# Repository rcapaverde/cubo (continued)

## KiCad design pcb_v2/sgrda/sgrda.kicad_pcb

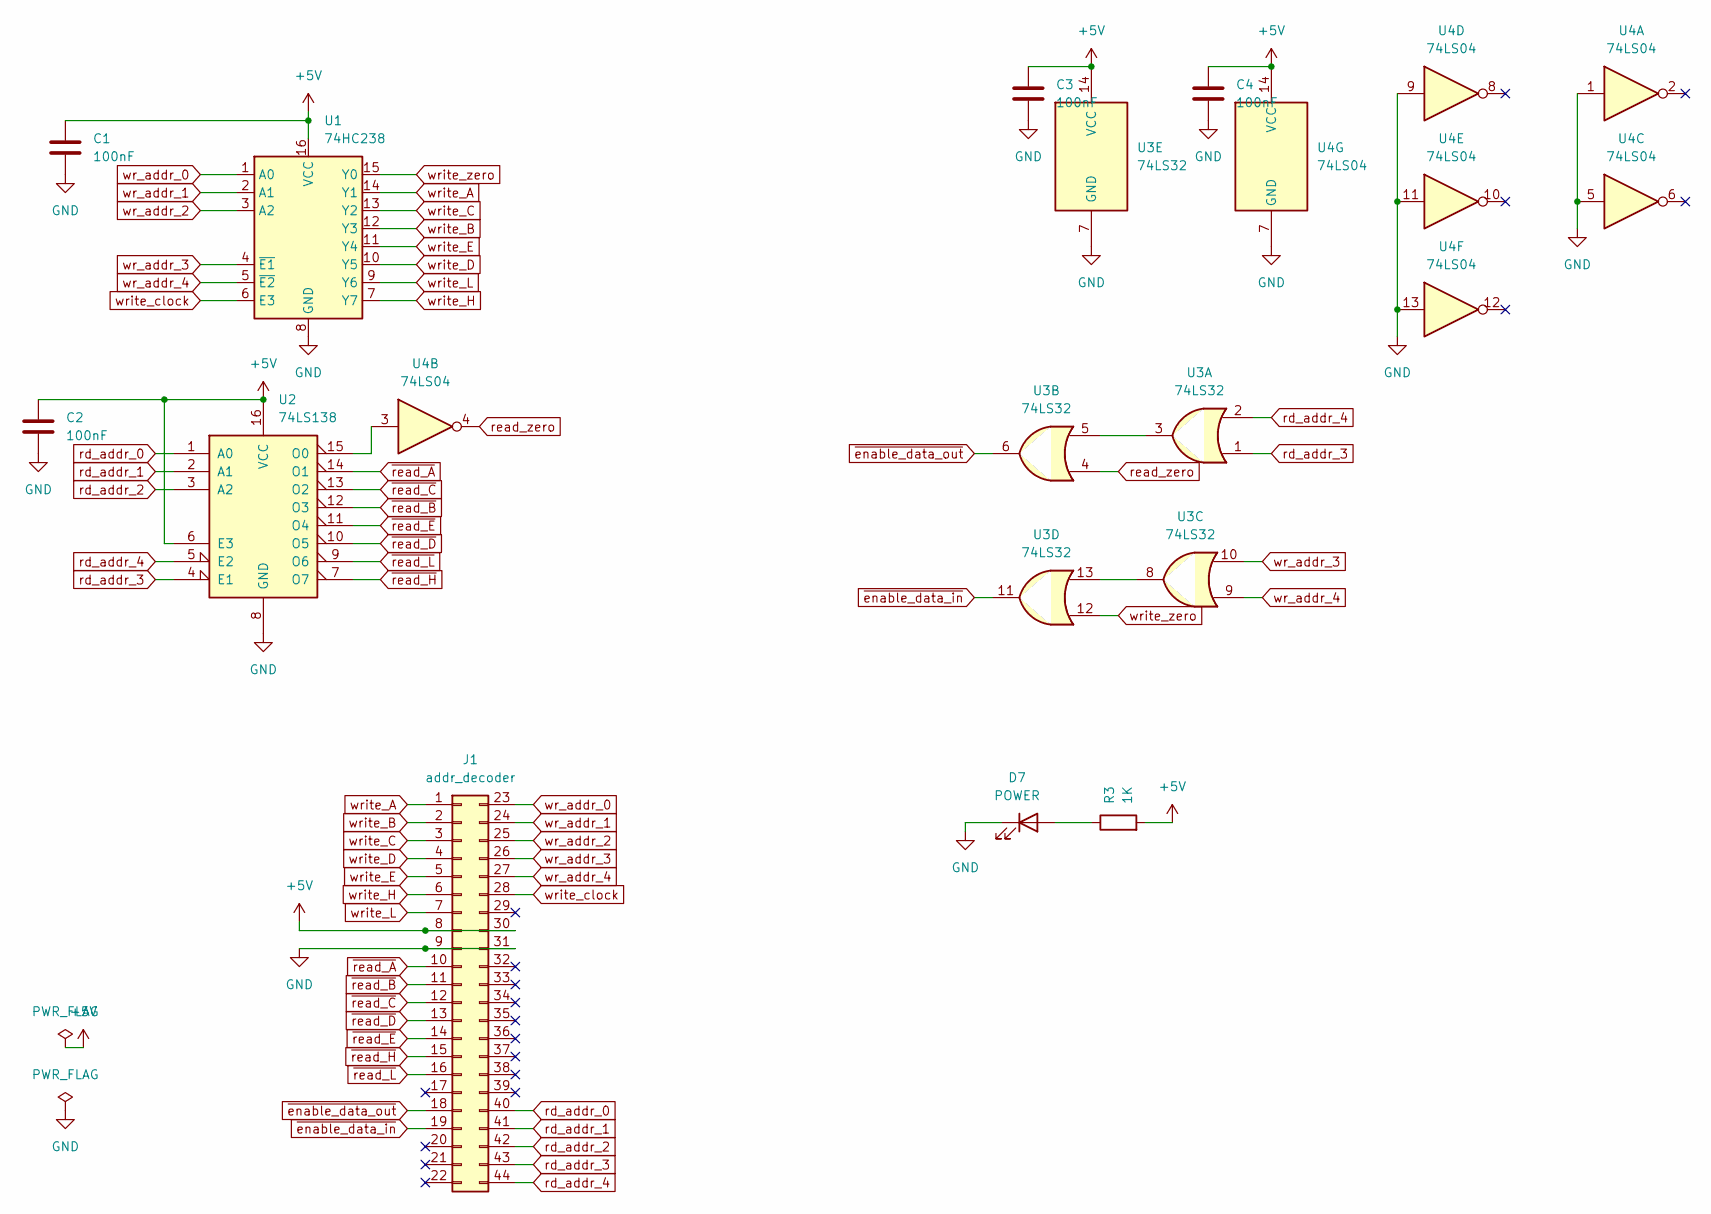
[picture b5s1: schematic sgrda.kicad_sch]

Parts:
C1, C2, C3, C4: 100nF; C_Disc_D4.7mm_W2.5mm_P5.00mm
D7: POWER; LED_D5.0mm
J1: addr_decoder; edge-connector-44
R3: 1K; R_Axial_DIN0207_L6.3mm_D2.5mm_P7.62mm_Horizontal
U1: 74HC238; DIP-16_W7.62mm
U2: 74LS138; DIP-16_W7.62mm
U3: 74LS32; DIP-14_W7.62mm
U4: 74LS04; DIP-14_W7.62mm

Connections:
+5V: C1.1, C2.1, C3.1, C4.1, J1.8, J1.30, R3.2, U1.16 (VCC), U2.6 (E3), U2.16 (VCC), U3.14 (VCC), U4.14 (VCC)
GND: C1.2, C2.2, C3.2, C4.2, D7.1 (K), J1.9, J1.31, U1.8 (GND), U2.8 (GND), U3.7 (GND), U4.1, U4.5, U4.7 (GND), U4.9, U4.11, U4.13
unnamed: D7.2 (A), R3.1
unnamed: U2.15 (O0), U4.3
unnamed: U3.3, U3.5
unnamed: U3.8, U3.13
rd_addr_0: J1.40, U2.1 (A0)
rd_addr_1: J1.41, U2.2 (A1)
rd_addr_2: J1.42, U2.3 (A2)
rd_addr_3: J1.43, U2.4 (E1), U3.1
rd_addr_4: J1.44, U2.5 (E2), U3.2
read_zero: U3.4, U4.4
wr_addr_0: J1.23, U1.1 (A0)
wr_addr_1: J1.24, U1.2 (A1)
wr_addr_2: J1.25, U1.3 (A2)
wr_addr_3: J1.26, U1.4 (~E1), U3.10
wr_addr_4: J1.27, U1.5 (~E2), U3.9
write_A: J1.1, U1.14 (Y1)
write_B: J1.2, U1.12 (Y3)
write_C: J1.3, U1.13 (Y2)
write_D: J1.4, U1.10 (Y5)
write_E: J1.5, U1.11 (Y4)
write_H: J1.6, U1.7 (Y7)
write_L: J1.7, U1.9 (Y6)
write_clock: J1.28, U1.6 (E3)
write_zero: U1.15 (Y0), U3.12
~enable_data_in: J1.19, U3.11
~enable_data_out: J1.18, U3.6
~read_A: J1.10, U2.14 (O1)
~read_B: J1.11, U2.12 (O3)
~read_C: J1.12, U2.13 (O2)
~read_D: J1.13, U2.10 (O5)
~read_E: J1.14, U2.11 (O4)
~read_H: J1.15, U2.7 (O7)
~read_L: J1.16, U2.9 (O6)

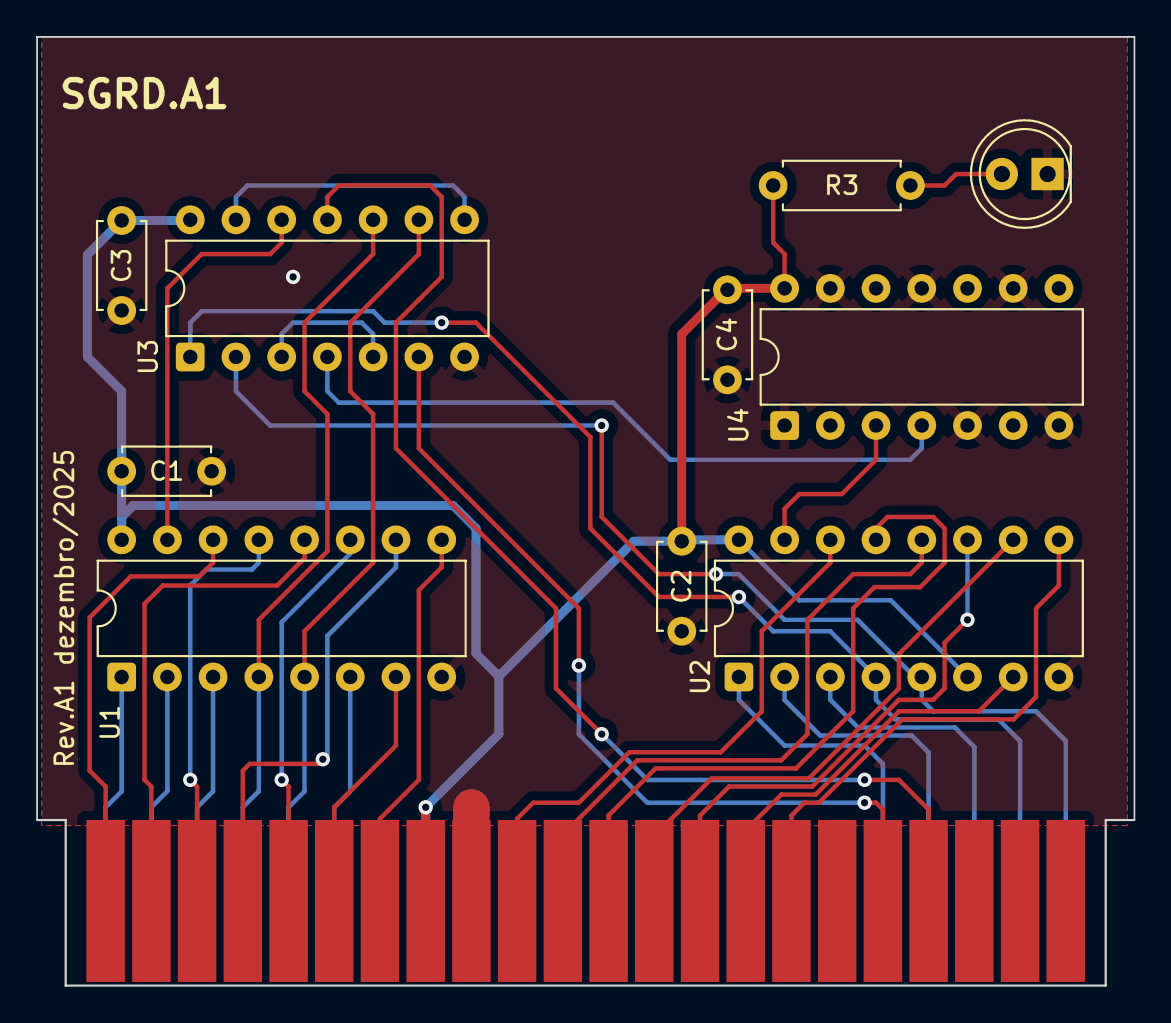
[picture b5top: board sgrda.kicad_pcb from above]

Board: 2 copper layers, 61.0 x 52.7 mm, 11 parts (0 on the bottom side), 35 nets.

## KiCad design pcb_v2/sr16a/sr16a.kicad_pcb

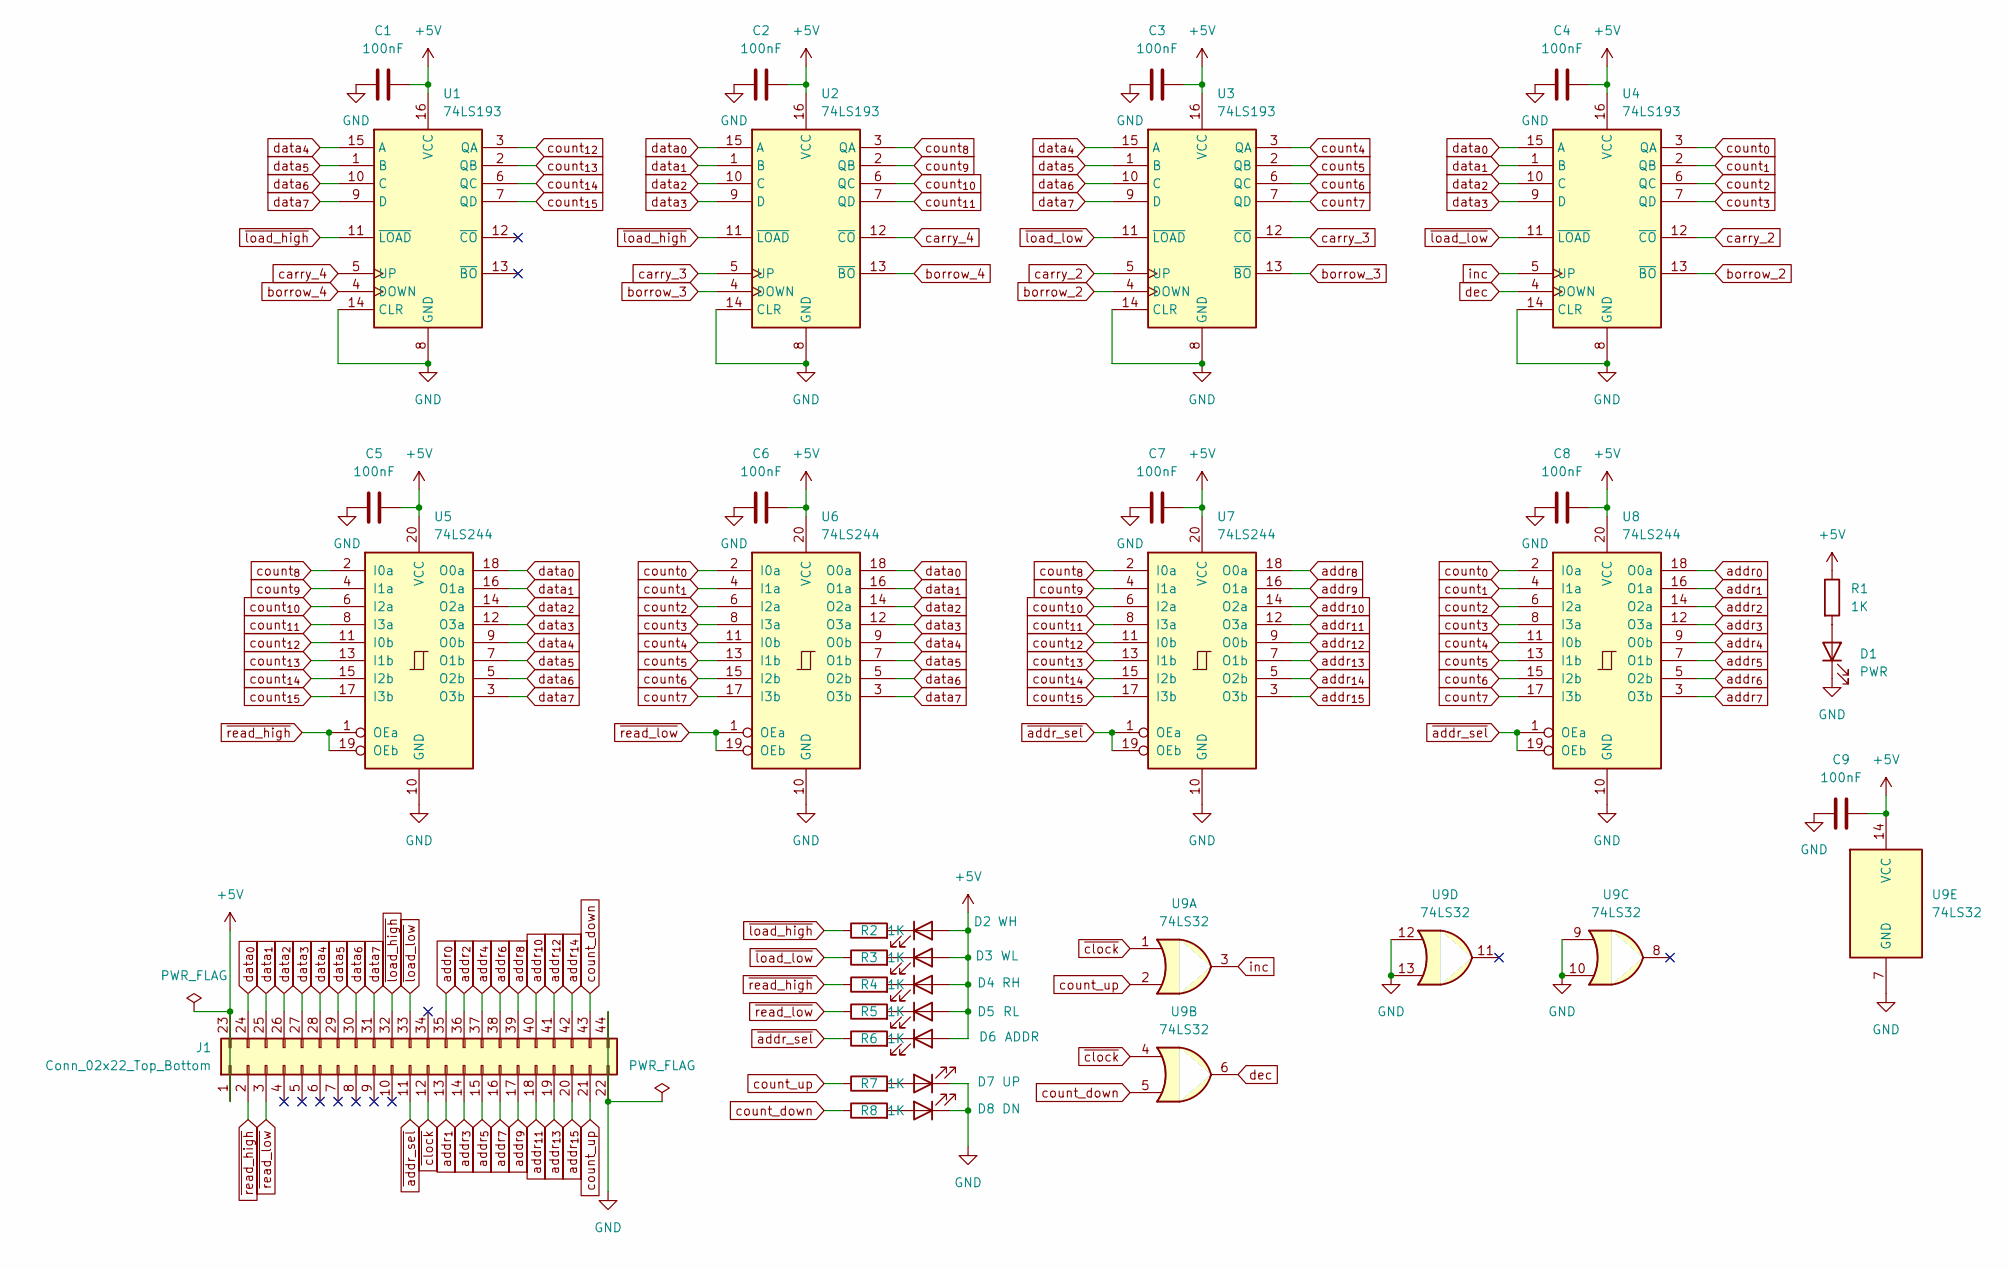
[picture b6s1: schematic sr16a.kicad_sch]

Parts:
C1, C2, C3, C4, C5, C6, C7, C8, C9: 100nF; C_Disc_D5.1mm_W3.2mm_P5.00mm
D1: PWR; LED_D5.0mm
D2: WH; LED_D5.0mm
D3: WL; LED_D5.0mm
D4: RH; LED_D5.0mm
D5: RL; LED_D5.0mm
D6: ADDR; LED_D5.0mm
D7: UP; LED_D5.0mm
D8: DN; LED_D5.0mm
J1: Conn_02x22_Top_Bottom; edge-connector-44
R1, R2, R3, R4, R5, R6, R7, R8: 1K; R_Axial_DIN0204_L3.6mm_D1.6mm_P7.62mm_Horizontal
U1, U2, U3, U4: 74LS193; DIP-16_W7.62mm
U5, U6, U7, U8: 74LS244; DIP-20_W7.62mm
U9: 74LS32; DIP-14_W7.62mm

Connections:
+5V: C1.2, C2.2, C3.2, C4.2, C5.2, C6.2, C7.2, C8.2, C9.2, D2.2 (A), D3.2 (A), D4.2 (A), D5.2 (A), D6.2 (A), J1.1, J1.23, R1.1, U1.16 (VCC), U2.16 (VCC), U3.16 (VCC), U4.16 (VCC), U5.20 (VCC), U6.20 (VCC), U7.20 (VCC), U8.20 (VCC), U9.14 (VCC)
GND: C1.1, C2.1, C3.1, C4.1, C5.1, C6.1, C7.1, C8.1, C9.1, D1.1 (K), D7.1 (K), D8.1 (K), J1.22, J1.44, U1.8 (GND), U1.14 (CLR), U2.8 (GND), U2.14 (CLR), U3.8 (GND), U3.14 (CLR), U4.8 (GND), U4.14 (CLR), U5.10 (GND), U6.10 (GND), U7.10 (GND), U8.10 (GND), U9.7 (GND), U9.9, U9.10, U9.12, U9.13
unnamed: D1.2 (A), R1.2
unnamed: D2.1 (K), R2.2
unnamed: D3.1 (K), R3.2
unnamed: D4.1 (K), R4.2
unnamed: D5.1 (K), R5.2
unnamed: D6.1 (K), R6.2
unnamed: D7.2 (A), R7.2
unnamed: D8.2 (A), R8.2
addr_{0}: J1.35, U8.18 (O0a)
addr_{1}: J1.13, U8.16 (O1a)
addr_{2}: J1.36, U8.14 (O2a)
addr_{3}: J1.14, U8.12 (O3a)
addr_{4}: J1.37, U8.9 (O0b)
addr_{5}: J1.15, U8.7 (O1b)
addr_{6}: J1.38, U8.5 (O2b)
addr_{7}: J1.16, U8.3 (O3b)
addr_{8}: J1.39, U7.18 (O0a)
addr_{9}: J1.17, U7.16 (O1a)
addr_{10}: J1.40, U7.14 (O2a)
addr_{11}: J1.18, U7.12 (O3a)
addr_{12}: J1.41, U7.9 (O0b)
addr_{13}: J1.19, U7.7 (O1b)
addr_{14}: J1.42, U7.5 (O2b)
addr_{15}: J1.20, U7.3 (O3b)
borrow_2: U3.4 (DOWN), U4.13 (~BO)
borrow_3: U2.4 (DOWN), U3.13 (~BO)
borrow_4: U1.4 (DOWN), U2.13 (~BO)
carry_2: U3.5 (UP), U4.12 (~CO)
carry_3: U2.5 (UP), U3.12 (~CO)
carry_4: U1.5 (UP), U2.12 (~CO)
count_down: J1.43, R8.1, U9.5
count_up: J1.21, R7.1, U9.2
count_{0}: U4.3 (QA), U6.2 (I0a), U8.2 (I0a)
count_{1}: U4.2 (QB), U6.4 (I1a), U8.4 (I1a)
count_{2}: U4.6 (QC), U6.6 (I2a), U8.6 (I2a)
count_{3}: U4.7 (QD), U6.8 (I3a), U8.8 (I3a)
count_{4}: U3.3 (QA), U6.11 (I0b), U8.11 (I0b)
count_{5}: U3.2 (QB), U6.13 (I1b), U8.13 (I1b)
count_{6}: U3.6 (QC), U6.15 (I2b), U8.15 (I2b)
count_{7}: U3.7 (QD), U6.17 (I3b), U8.17 (I3b)
count_{8}: U2.3 (QA), U5.2 (I0a), U7.2 (I0a)
count_{9}: U2.2 (QB), U5.4 (I1a), U7.4 (I1a)
count_{10}: U2.6 (QC), U5.6 (I2a), U7.6 (I2a)
count_{11}: U2.7 (QD), U5.8 (I3a), U7.8 (I3a)
count_{12}: U1.3 (QA), U5.11 (I0b), U7.11 (I0b)
count_{13}: U1.2 (QB), U5.13 (I1b), U7.13 (I1b)
count_{14}: U1.6 (QC), U5.15 (I2b), U7.15 (I2b)
count_{15}: U1.7 (QD), U5.17 (I3b), U7.17 (I3b)
data_{0}: J1.24, U2.15 (A), U4.15 (A), U5.18 (O0a), U6.18 (O0a)
data_{1}: J1.25, U2.1 (B), U4.1 (B), U5.16 (O1a), U6.16 (O1a)
data_{2}: J1.26, U2.10 (C), U4.10 (C), U5.14 (O2a), U6.14 (O2a)
data_{3}: J1.27, U2.9 (D), U4.9 (D), U5.12 (O3a), U6.12 (O3a)
data_{4}: J1.28, U1.15 (A), U3.15 (A), U5.9 (O0b), U6.9 (O0b)
data_{5}: J1.29, U1.1 (B), U3.1 (B), U5.7 (O1b), U6.7 (O1b)
data_{6}: J1.30, U1.10 (C), U3.10 (C), U5.5 (O2b), U6.5 (O2b)
data_{7}: J1.31, U1.9 (D), U3.9 (D), U5.3 (O3b), U6.3 (O3b)
dec: U4.4 (DOWN), U9.6
inc: U4.5 (UP), U9.3
~addr_sel: J1.11, R6.1, U7.1 (OEa), U7.19 (OEb), U8.1 (OEa), U8.19 (OEb)
~clock: J1.12, U9.1, U9.4
~load_high: J1.32, R2.1, U1.11 (~LOAD), U2.11 (~LOAD)
~load_low: J1.33, R3.1, U3.11 (~LOAD), U4.11 (~LOAD)
~read_high: J1.2, R4.1, U5.1 (OEa), U5.19 (OEb)
~read_low: J1.3, R5.1, U6.1 (OEa), U6.19 (OEb)

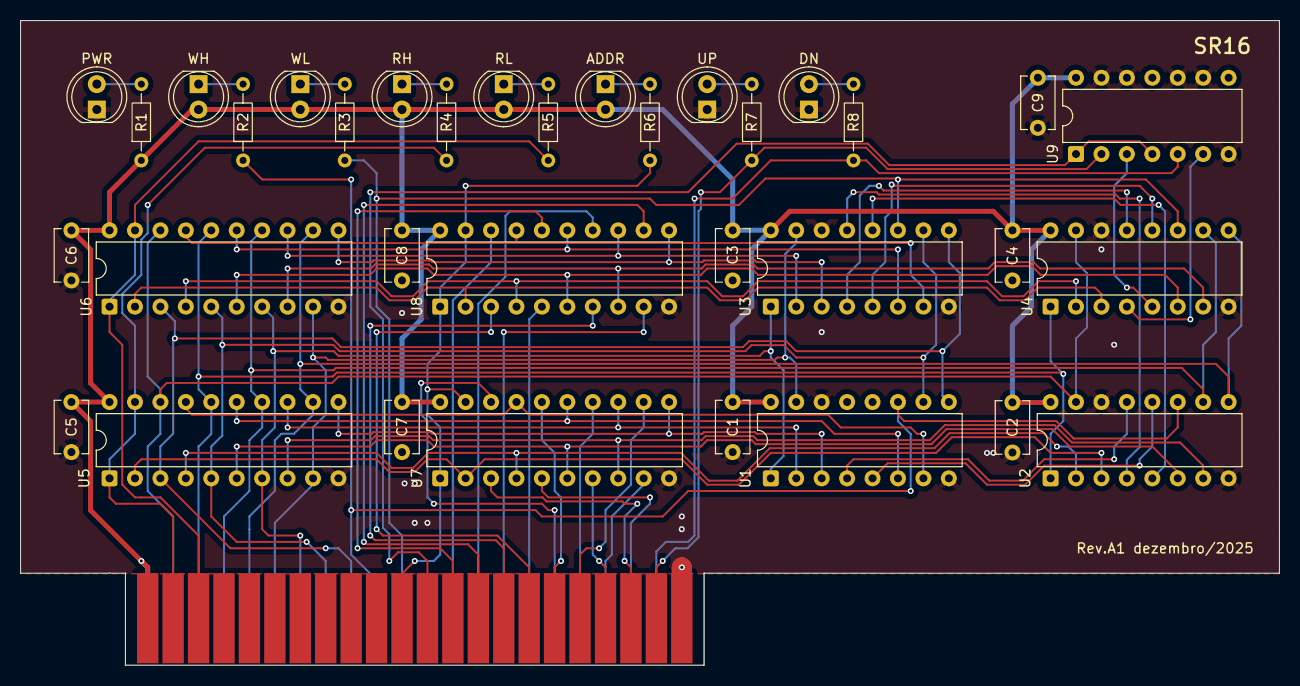
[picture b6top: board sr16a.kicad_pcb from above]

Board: 2 copper layers, 125.7 x 64.4 mm, 35 parts (0 on the bottom side), 66 nets.

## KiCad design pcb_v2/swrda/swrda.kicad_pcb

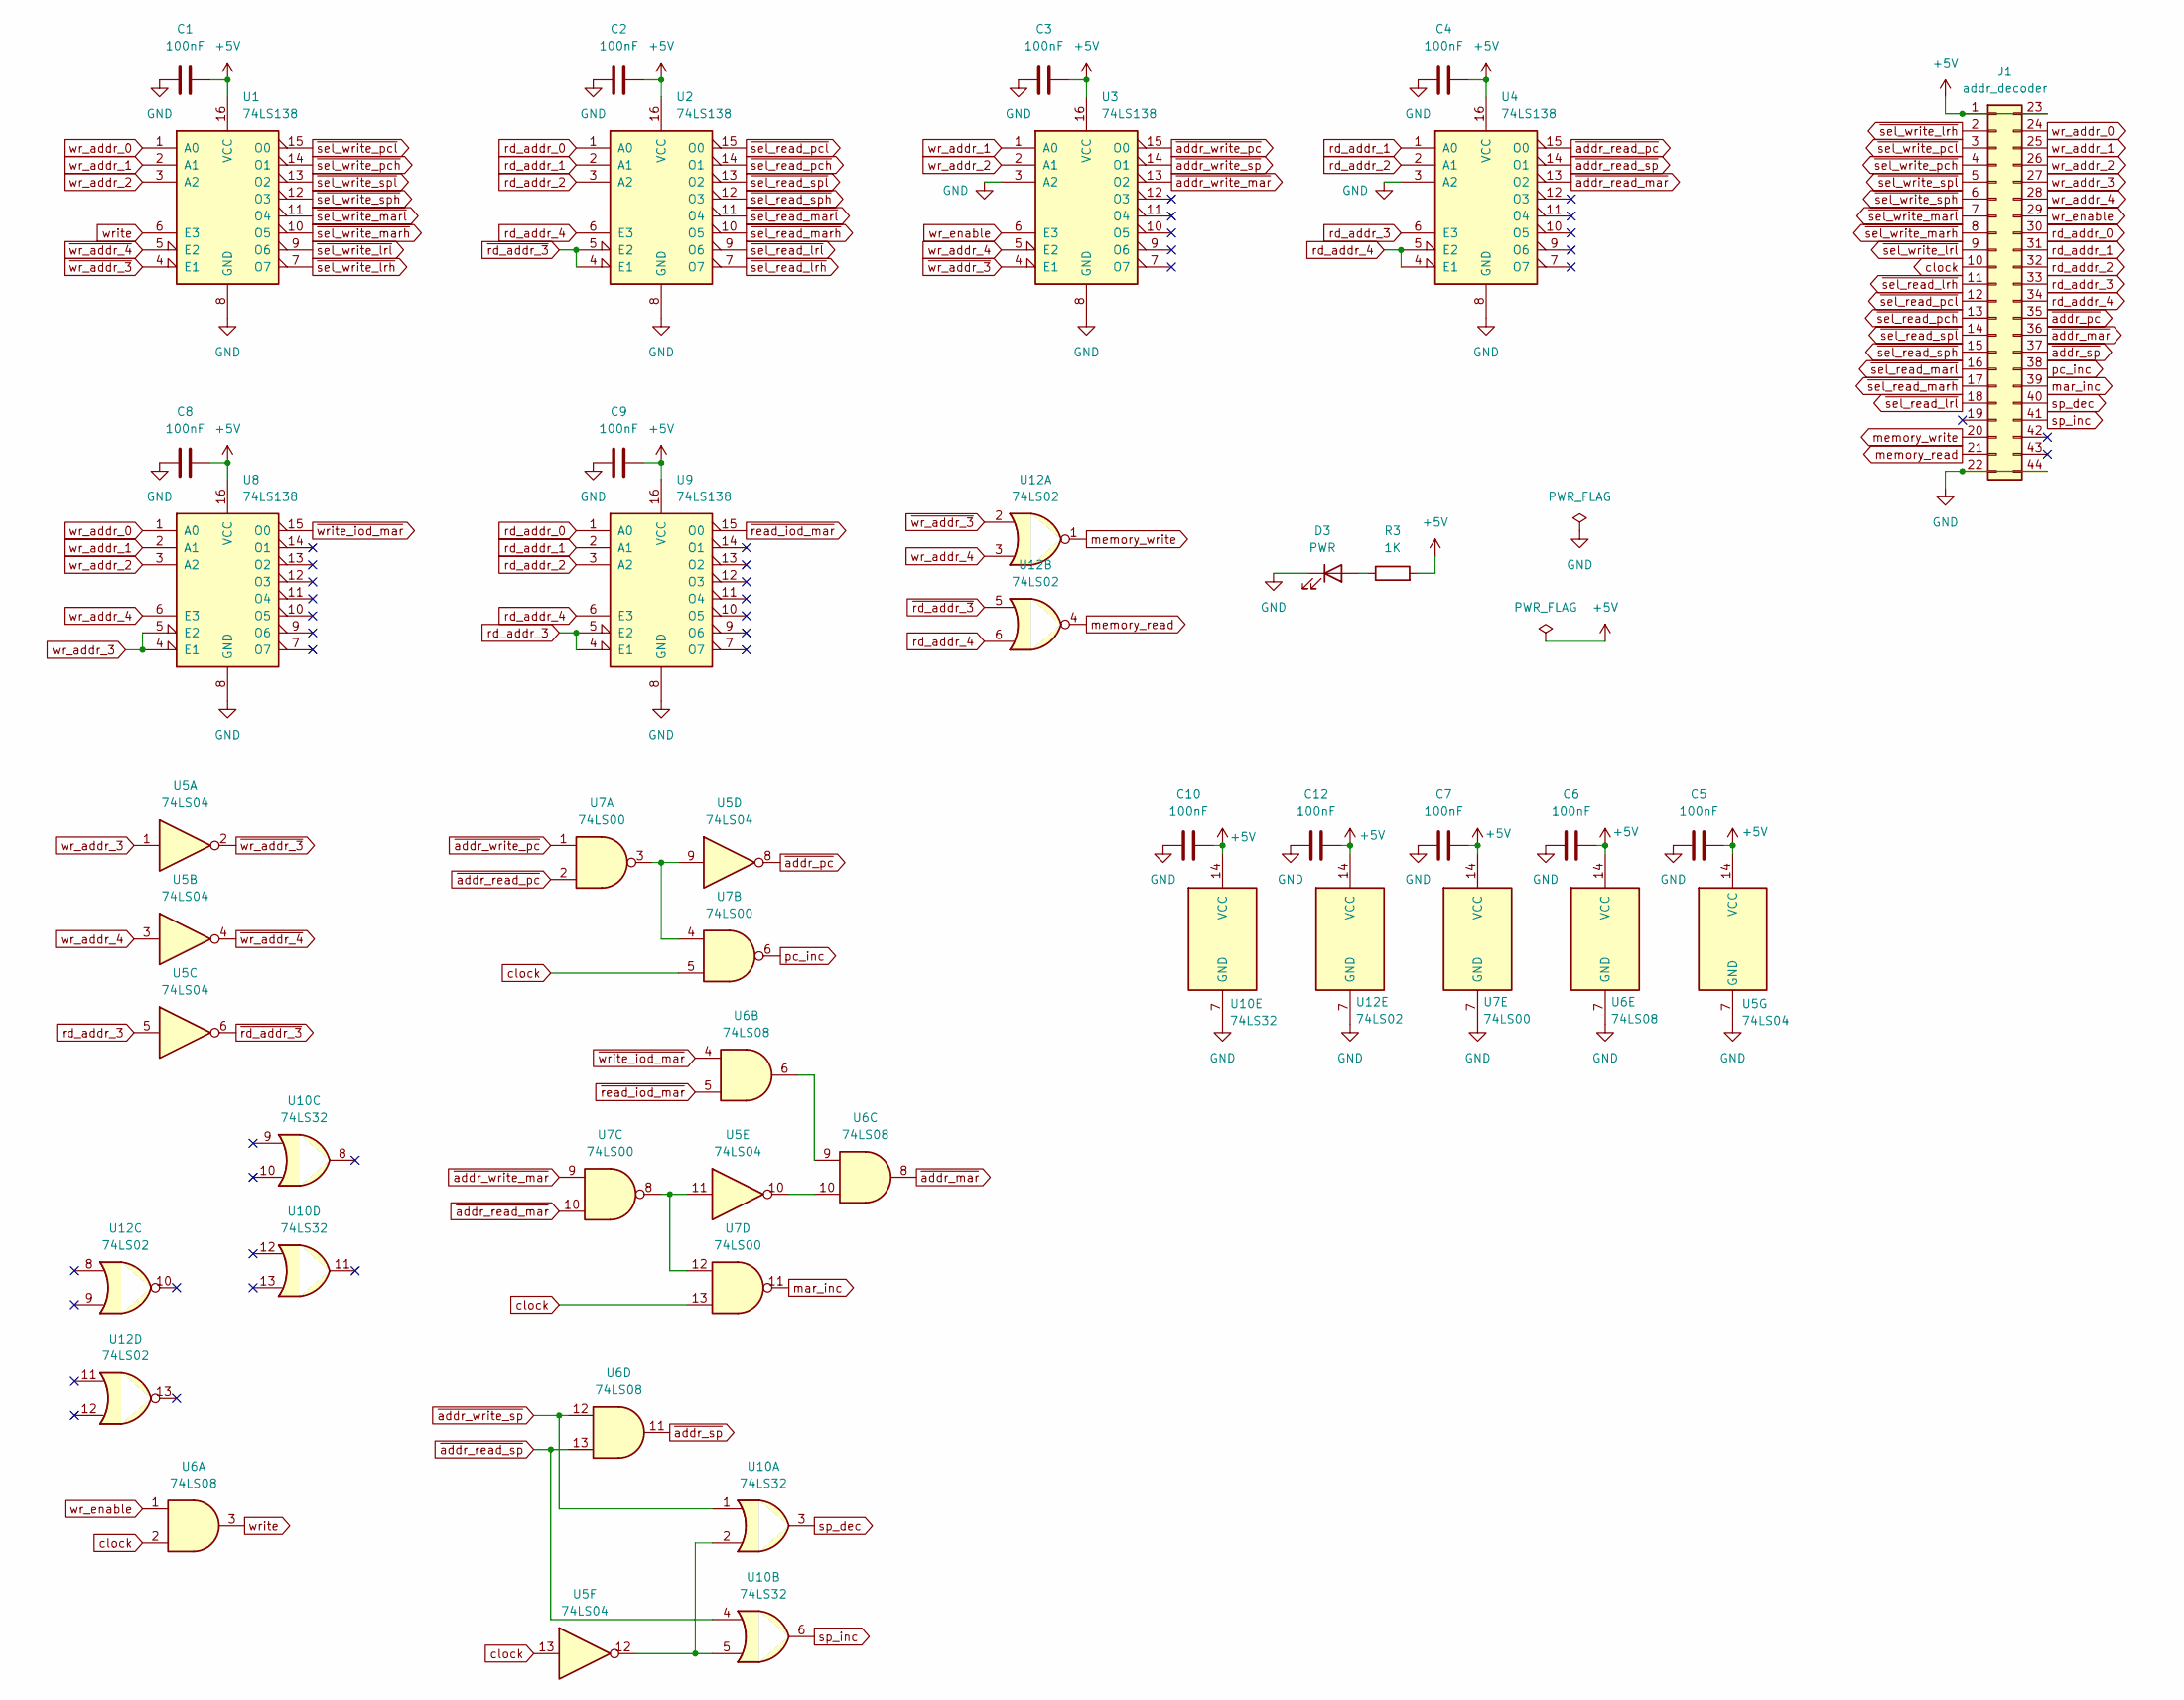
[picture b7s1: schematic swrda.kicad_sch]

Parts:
C1, C2, C3, C4, C5, C6, C7, C8, C9, C10, C12: 100nF; C_Disc_D5.1mm_W3.2mm_P5.00mm
D3: PWR; LED_D5.0mm
J1: addr_decoder; edge-connector-44
R3: 1K; R_Axial_DIN0207_L6.3mm_D2.5mm_P7.62mm_Horizontal
U1, U2, U3, U4, U8, U9: 74LS138; DIP-16_W7.62mm
U5: 74LS04; DIP-14_W7.62mm
U6: 74LS08; DIP-14_W7.62mm
U7: 74LS00; DIP-14_W7.62mm
U10: 74LS32; DIP-14_W7.62mm
U12: 74LS02; DIP-14_W7.62mm

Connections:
+5V: C1.2, C2.2, C3.2, C4.2, C5.2, C6.2, C7.2, C8.2, C9.2, C10.2, C12.2, J1.1, J1.23, R3.2, U1.16 (VCC), U2.16 (VCC), U3.16 (VCC), U4.16 (VCC), U5.14 (VCC), U6.14 (VCC), U7.14 (VCC), U8.16 (VCC), U9.16 (VCC), U10.14 (VCC), U12.14 (VCC)
GND: C1.1, C2.1, C3.1, C4.1, C5.1, C6.1, C7.1, C8.1, C9.1, C10.1, C12.1, D3.1 (K), J1.22, J1.44, U1.8 (GND), U2.8 (GND), U3.3 (A2), U3.8 (GND), U4.3 (A2), U4.8 (GND), U5.7 (GND), U6.7 (GND), U7.7 (GND), U8.8 (GND), U9.8 (GND), U10.7 (GND), U12.7 (GND)
unnamed: D3.2 (A), R3.1
unnamed: U5.9, U7.3, U7.4
unnamed: U5.10, U6.10
unnamed: U5.11, U7.8, U7.12
unnamed: U6.6, U6.9
unnamed: U5.12, U10.2, U10.5
clock: J1.10, U5.13, U6.2, U7.5, U7.13
mar_inc: J1.39, U7.11
memory_read: J1.21, U12.4
memory_write: J1.20, U12.1
pc_inc: J1.38, U7.6
rd_addr_0: J1.30, U2.1 (A0), U9.1 (A0)
rd_addr_1: J1.31, U2.2 (A1), U4.1 (A0), U9.2 (A1)
rd_addr_2: J1.32, U2.3 (A2), U4.2 (A1), U9.3 (A2)
rd_addr_3: J1.33, U4.6 (E3), U5.5, U9.4 (E1), U9.5 (E2)
rd_addr_4: J1.34, U2.6 (E3), U4.4 (E1), U4.5 (E2), U9.6 (E3), U12.6
sp_dec: J1.40, U10.3
sp_inc: J1.41, U10.6
wr_addr_0: J1.24, U1.1 (A0), U8.1 (A0)
wr_addr_1: J1.25, U1.2 (A1), U3.1 (A0), U8.2 (A1)
wr_addr_2: J1.26, U1.3 (A2), U3.2 (A1), U8.3 (A2)
wr_addr_3: J1.27, U5.1, U8.4 (E1), U8.5 (E2)
wr_addr_4: J1.28, U3.5 (E2), U5.3, U8.6 (E3), U12.3
wr_enable: J1.29, U3.6 (E3), U6.1
write: U1.6 (E3), U6.3
~addr_mar: J1.36, U6.8
~addr_pc: J1.35, U5.8
~addr_read_mar: U4.13 (O2), U7.10
~addr_read_pc: U4.15 (O0), U7.2
~addr_read_sp: U4.14 (O1), U6.13, U10.4
~addr_sp: J1.37, U6.11
~addr_write_mar: U3.13 (O2), U7.9
~addr_write_pc: U3.15 (O0), U7.1
~addr_write_sp: U3.14 (O1), U6.12, U10.1
~rd_addr_3: U2.4 (E1), U2.5 (E2), U5.6, U12.5
~read_iod_mar: U6.5, U9.15 (O0)
~sel_read_lrh: J1.11, U2.7 (O7)
~sel_read_lrl: J1.18, U2.9 (O6)
~sel_read_marh: J1.17, U2.10 (O5)
~sel_read_marl: J1.16, U2.11 (O4)
~sel_read_pch: J1.13, U2.14 (O1)
~sel_read_pcl: J1.12, U2.15 (O0)
~sel_read_sph: J1.15, U2.12 (O3)
~sel_read_spl: J1.14, U2.13 (O2)
~sel_write_lrh: J1.2, U1.7 (O7)
~sel_write_lrl: J1.9, U1.9 (O6)
~sel_write_marh: J1.8, U1.10 (O5)
~sel_write_marl: J1.7, U1.11 (O4)
~sel_write_pch: J1.4, U1.14 (O1)
~sel_write_pcl: J1.3, U1.15 (O0)
~sel_write_sph: J1.6, U1.12 (O3)
~sel_write_spl: J1.5, U1.13 (O2)
~wr_addr_3: U1.4 (E1), U3.4 (E1), U5.2, U12.2
~wr_addr_4: U1.5 (E2), U5.4
~write_iod_mar: U6.4, U8.15 (O0)

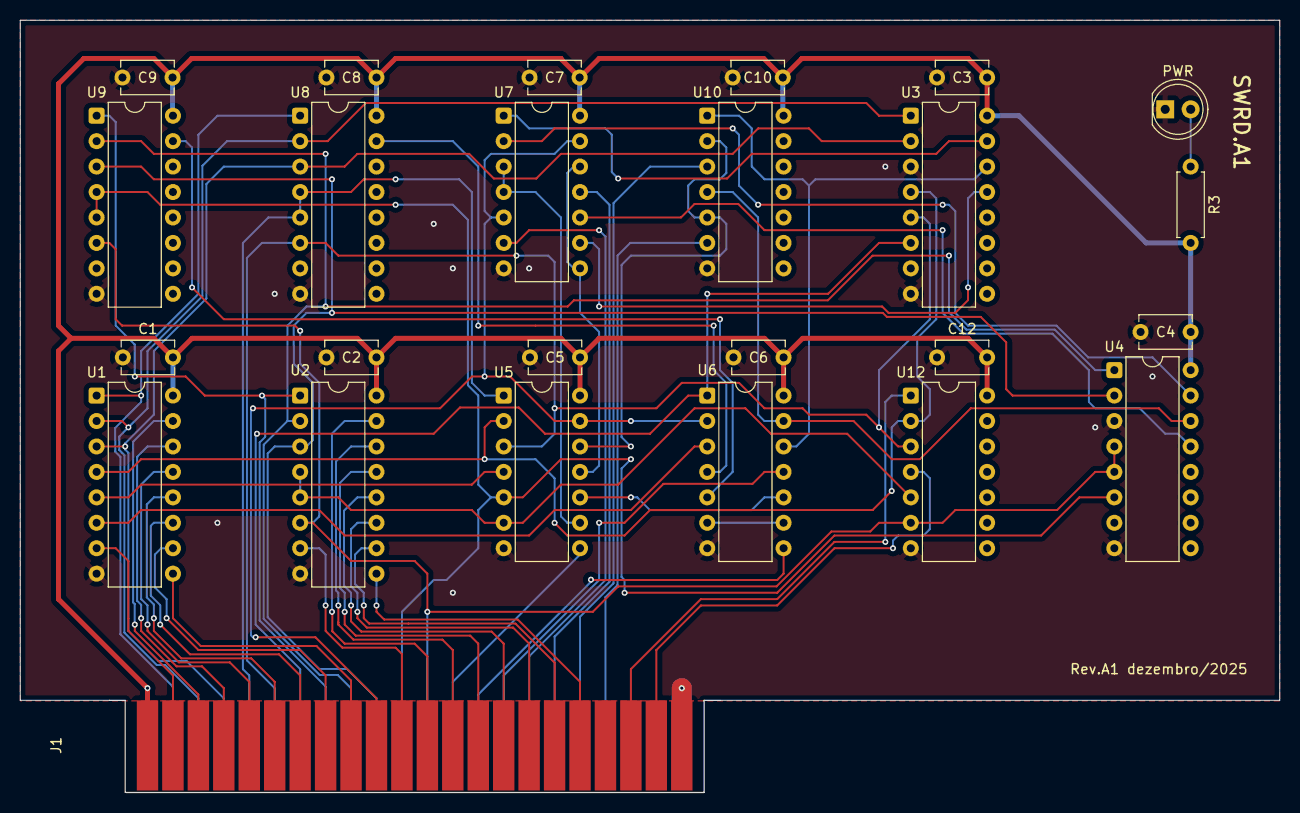
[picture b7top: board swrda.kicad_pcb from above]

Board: 2 copper layers, 125.7 x 77.1 mm, 25 parts (0 on the bottom side), 57 nets.

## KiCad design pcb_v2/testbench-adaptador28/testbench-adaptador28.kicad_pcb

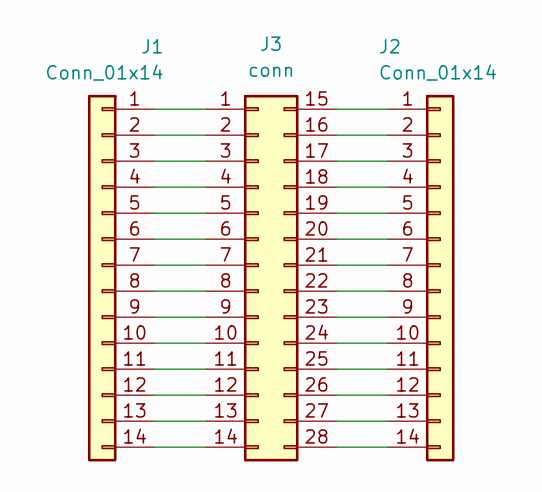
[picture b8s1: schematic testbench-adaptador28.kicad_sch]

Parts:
J1, J2: Conn_01x14; PinHeader_1x14_P2.54mm_Vertical
J3: conn; male-edge-connector-28

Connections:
unnamed: J1.1, J3.1
unnamed: J1.2, J3.2
unnamed: J1.3, J3.3
unnamed: J1.4, J3.4
unnamed: J1.5, J3.5
unnamed: J1.6, J3.6
unnamed: J1.7, J3.7
unnamed: J1.8, J3.8
unnamed: J1.9, J3.9
unnamed: J1.10, J3.10
unnamed: J1.11, J3.11
unnamed: J1.12, J3.12
unnamed: J1.13, J3.13
unnamed: J1.14, J3.14
unnamed: J2.1, J3.15
unnamed: J2.2, J3.16
unnamed: J2.3, J3.17
unnamed: J2.4, J3.18
unnamed: J2.5, J3.19
unnamed: J2.6, J3.20
unnamed: J2.7, J3.21
unnamed: J2.8, J3.22
unnamed: J2.9, J3.23
unnamed: J2.10, J3.24
unnamed: J2.11, J3.25
unnamed: J2.12, J3.26
unnamed: J2.13, J3.27
unnamed: J2.14, J3.28

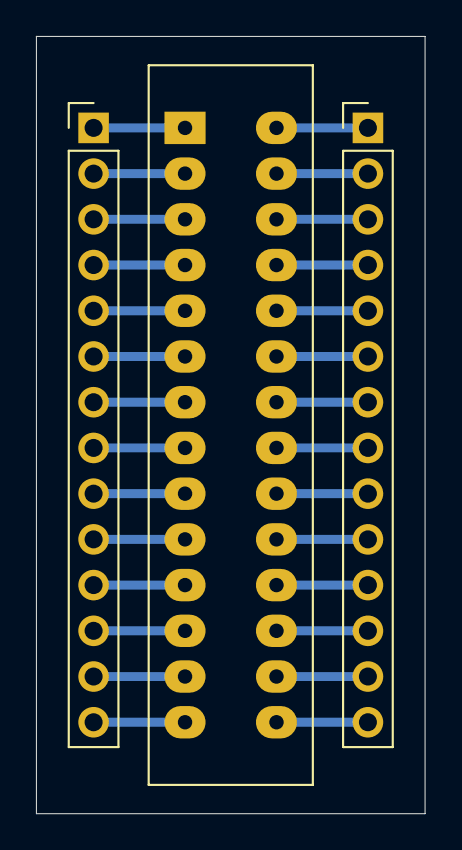
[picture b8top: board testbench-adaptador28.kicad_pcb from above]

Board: 2 copper layers, 21.6 x 43.2 mm, 3 parts (0 on the bottom side), 28 nets.
